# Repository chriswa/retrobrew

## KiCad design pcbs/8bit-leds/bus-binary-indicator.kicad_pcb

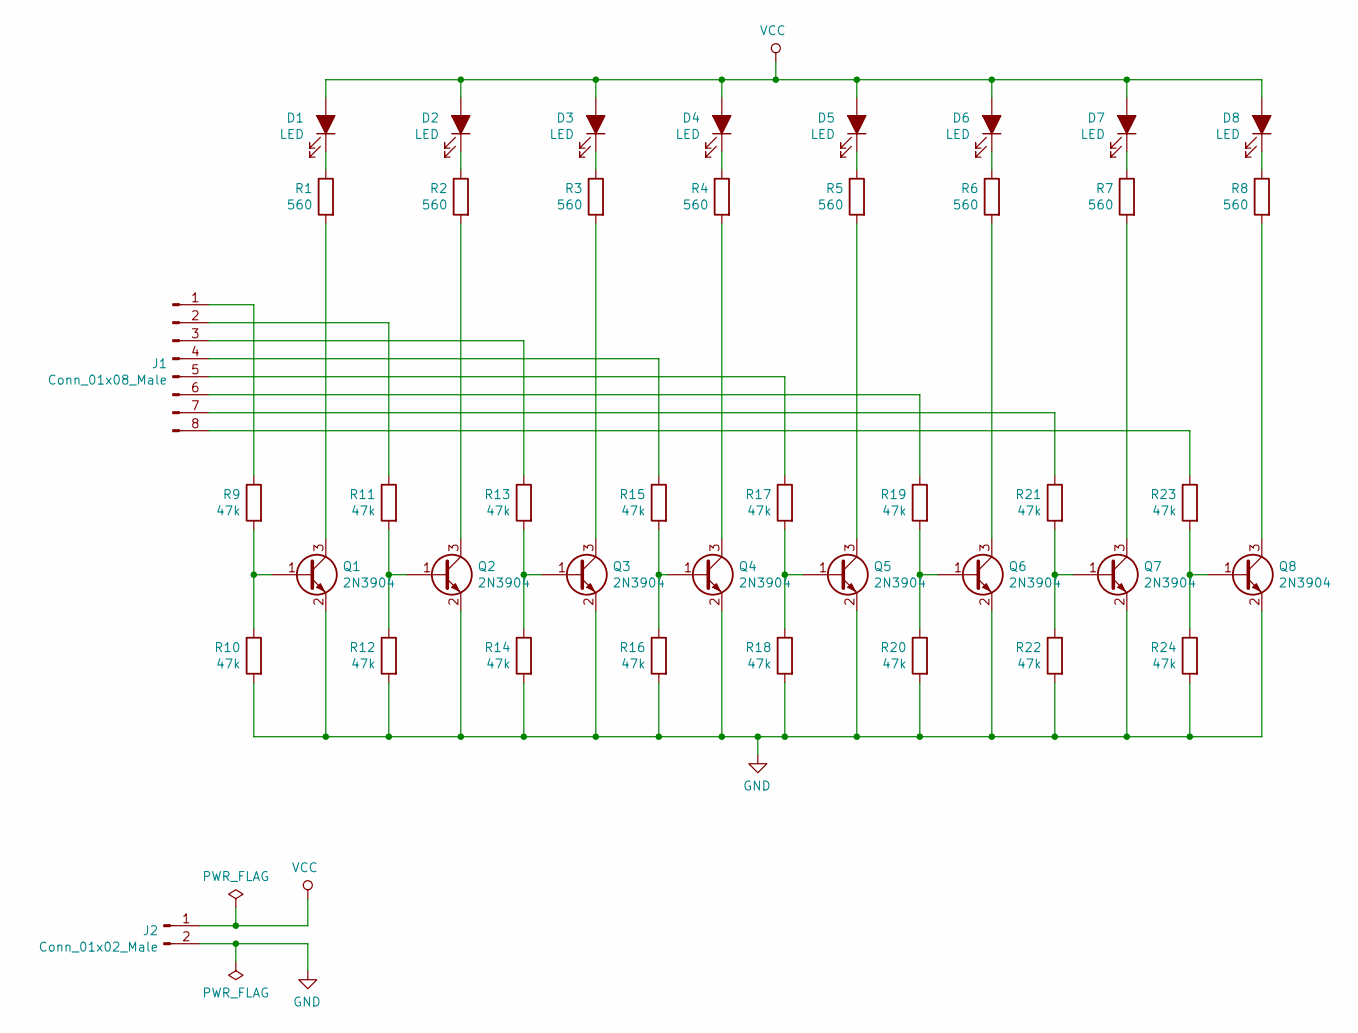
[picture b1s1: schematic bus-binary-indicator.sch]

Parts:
D1, D2, D3, D4, D5, D6, D7, D8: LED; LED_0603_1608Metric
J1: Conn_01x08_Male; PinHeader_1x08_P2.54mm_Vertical
J2: Conn_01x02_Male; PinHeader_1x02_P2.54mm_Vertical
Q1, Q2, Q3, Q4, Q5, Q6, Q7, Q8: 2N3904; SOT-23
R1, R2, R3, R4, R5, R6, R7, R8: 560; R_0402_1005Metric
R9, R10, R11, R12, R13, R14, R15, R16, R17, R18, R19, R20, R21, R22, R23, R24: 47k; R_0402_1005Metric

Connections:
GND: J2.2, Q1.2 (E), Q2.2 (E), Q3.2 (E), Q4.2 (E), Q5.2 (E), Q6.2 (E), Q7.2 (E), Q8.2 (E), R10.2, R12.2, R14.2, R16.2, R18.2, R20.2, R22.2, R24.2; also elsewhere on the board
unnamed: D1.1 (K), R1.1
unnamed: D2.1 (K), R2.1
unnamed: D3.1 (K), R3.1
unnamed: D4.1 (K), R4.1
unnamed: D5.1 (K), R5.1
unnamed: D6.1 (K), R6.1
unnamed: D7.1 (K), R7.1
unnamed: D8.1 (K), R8.1
unnamed: J1.1, R9.1
unnamed: J1.2, R11.1
unnamed: J1.3, R13.1
unnamed: J1.4, R15.1
unnamed: J1.5, R17.1
unnamed: J1.6, R19.1
unnamed: J1.7, R21.1
unnamed: J1.8, R23.1
unnamed: Q1.1 (B), R9.2, R10.1
unnamed: Q1.3 (C), R1.2
unnamed: Q2.1 (B), R11.2, R12.1
unnamed: Q2.3 (C), R2.2
unnamed: Q3.1 (B), R13.2, R14.1
unnamed: Q3.3 (C), R3.2
unnamed: Q4.1 (B), R15.2, R16.1
unnamed: Q4.3 (C), R4.2
unnamed: Q5.1 (B), R17.2, R18.1
unnamed: Q5.3 (C), R5.2
unnamed: Q6.1 (B), R19.2, R20.1
unnamed: Q6.3 (C), R6.2
unnamed: Q7.1 (B), R21.2, R22.1
unnamed: Q7.3 (C), R7.2
unnamed: Q8.1 (B), R23.2, R24.1
unnamed: Q8.3 (C), R8.2
VCC: D1.2 (A), D2.2 (A), D3.2 (A), D4.2 (A), D5.2 (A), D6.2 (A), D7.2 (A), D8.2 (A), J2.1; also elsewhere on the board

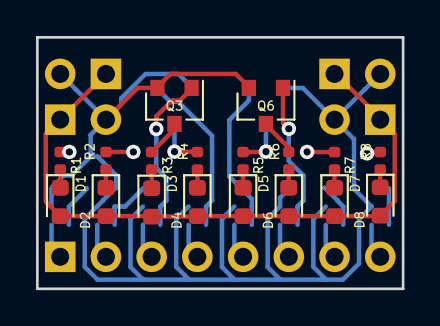
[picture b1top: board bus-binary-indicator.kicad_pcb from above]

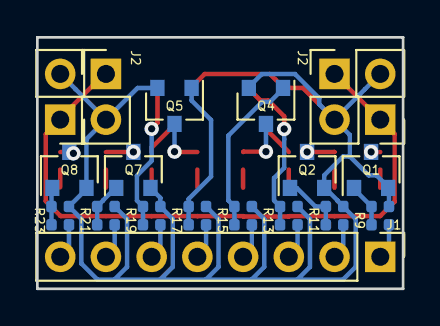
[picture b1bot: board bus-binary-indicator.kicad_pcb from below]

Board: 2 copper layers, 20.3 x 14.0 mm, 45 parts (27 on the bottom side), 34 nets.

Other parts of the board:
J2#2, J2#3, J2#4: Conn_01x02_Male; PinHeader_1x02_P2.54mm_Vertical

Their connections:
GND: J2#2.2, J2#3.2, J2#4.2; also elsewhere on the board
VCC: J2#2.1, J2#3.1, J2#4.1; also elsewhere on the board

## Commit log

2019-03-12 storeKbdInc for fast ram programming
2019-03-12 storeKbdIncA also writes to A so we can check the value we just wrote to memory
2019-03-26 many change. much feature
2019-04-07 final changes before teardown
2019-04-12 it works!
2019-04-19 final rewiring
2019-04-23 works
2019-05-06 pcbs
2019-05-08 works!
2019-05-16 new keyboard rom writer
2019-05-21 phase 3 complete
2019-05-21 microcode fix for ABload*
2019-05-22 hex editor progress
2019-05-24 kbd fw, harness stl
2019-05-24 scaling stl
2019-05-24 scaling stl 100
2019-05-27 adding ctrl+alt+delete
2019-05-28 double harness
2019-07-27 stack + c registers
2019-08-03 pre-uploader change
2019-08-07 uploader now takes target program as arg
2020-03-16 Bump minimist from 1.2.0 to 1.2.2
    Bumps [minimist](https://github.com/substack/minimist) from 1.2.0 to 1.2.2.
    - [Release notes](https://github.com/substack/minimist/releases)
    - [Commits](https://github.com/substack/minimist/compare/1.2.0...1.2.2)
2020-04-04 Bump minimist from 1.2.0 to 1.2.3
    Bumps [minimist](https://github.com/substack/minimist) from 1.2.0 to 1.2.3.
    - [Release notes](https://github.com/substack/minimist/releases)
    - [Commits](https://github.com/substack/minimist/compare/1.2.0...1.2.3)
2020-12-11 Bump ini from 1.3.5 to 1.3.7
    Bumps [ini](https://github.com/isaacs/ini) from 1.3.5 to 1.3.7.
    - [Release notes](https://github.com/isaacs/ini/releases)
    - [Commits](https://github.com/isaacs/ini/compare/v1.3.5...v1.3.7)
2020-12-11 Bump ini from 1.3.5 to 1.3.7 in /programs
    Bumps [ini](https://github.com/isaacs/ini) from 1.3.5 to 1.3.7.
    - [Release notes](https://github.com/isaacs/ini/releases)
    - [Commits](https://github.com/isaacs/ini/compare/v1.3.5...v1.3.7)
2022-04-10 Bump minimist from 1.2.0 to 1.2.6
    Bumps [minimist](https://github.com/substack/minimist) from 1.2.0 to 1.2.6.
    - [Release notes](https://github.com/substack/minimist/releases)
    - [Commits](https://github.com/substack/minimist/compare/1.2.0...1.2.6)
    ---
    updated-dependencies:
    - dependency-name: minimist
